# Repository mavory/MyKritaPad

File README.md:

# MyKritaPad

MyKritaPad is a custom 9-key macropad powered by a Seeed Studio XIAO RP2040!
It includes 9 mechanical switches wired through 9 diodes and two EC11 rotary encoders for additional input control. ⭐

## Why did I do this?

I wanted to try something completely new that I had never done before. I was very interested in how everyone can create their own mini keyboard, so I tried it too.

## Notes

I started on Friday, October 28th. That day I saw that I could make my own mini keyboard, I registered and downloaded the programs. Then I opened KiCad and told myself that I would never do it (it was like flying a plane for the first time). Well, I had to overcome myself and started creating with it. At first it was terrible, but somehow I got over it.

Unfortunately, on October 29th I got sick and couldn't do anything at all, but on November 30th I overcame myself and started creating the first designs for my KritaPad. When I created it with it, I moved to Fusion, which I also looked into, what it was... Somehow I did it, even though I don't want to think about it.

Then on December 1st I overcame myself and spent the whole day at the computer to finish it. In the evening I finished and submitted the project.

## Features
- 9 mechanical keys  
- 9x diodes for proper key isolation  
- 12x SK6812 MINI-E addressable RGB LEDs (RGB LEDs unfortunately I had a bad footprint and because of that my neopixels don't work)  
- 2x EC11 rotary encoders
- Powered by Seeed Studio XIAO RP2040  
- Designed for use with KMK or custom firmware  

## PCB
The PCB is designed in KiCad and includes:
- 9 key switch footprints  
- diode matrix wiring  
- daisy-chained SK6812 MINI-E LEDs 
- pins for two rotary encoders  
- XIAO RP2040 as the main controller  

### Schematic

### PCB Layout
(I know, it's terrible.)

### Top view

## Firmware
The macropad can be programmed using KMK,... or any custom RP2040 firmware.  

## BOM

### Custom Components
- 1x Custom PCB  
- 1x 3D printed case (top, bottom - Black)
- 9x keycaps  

### COTS Components
- 9x mechanical switches (MX style)  
- 9x Blank DSA keycaps
- 9x 1N4148 diodes  
- 12x SK6812 MINI-E LEDs  
- 2x EC11 rotary encoders  
- 1x Seeed Studio XIAO RP2040    
- 4x M3 x 6mm Screws
- 4x M3x5mx4mm heatset inserts

## Info
This macropad is made as part of the Hack Club Hackpad program! ✨

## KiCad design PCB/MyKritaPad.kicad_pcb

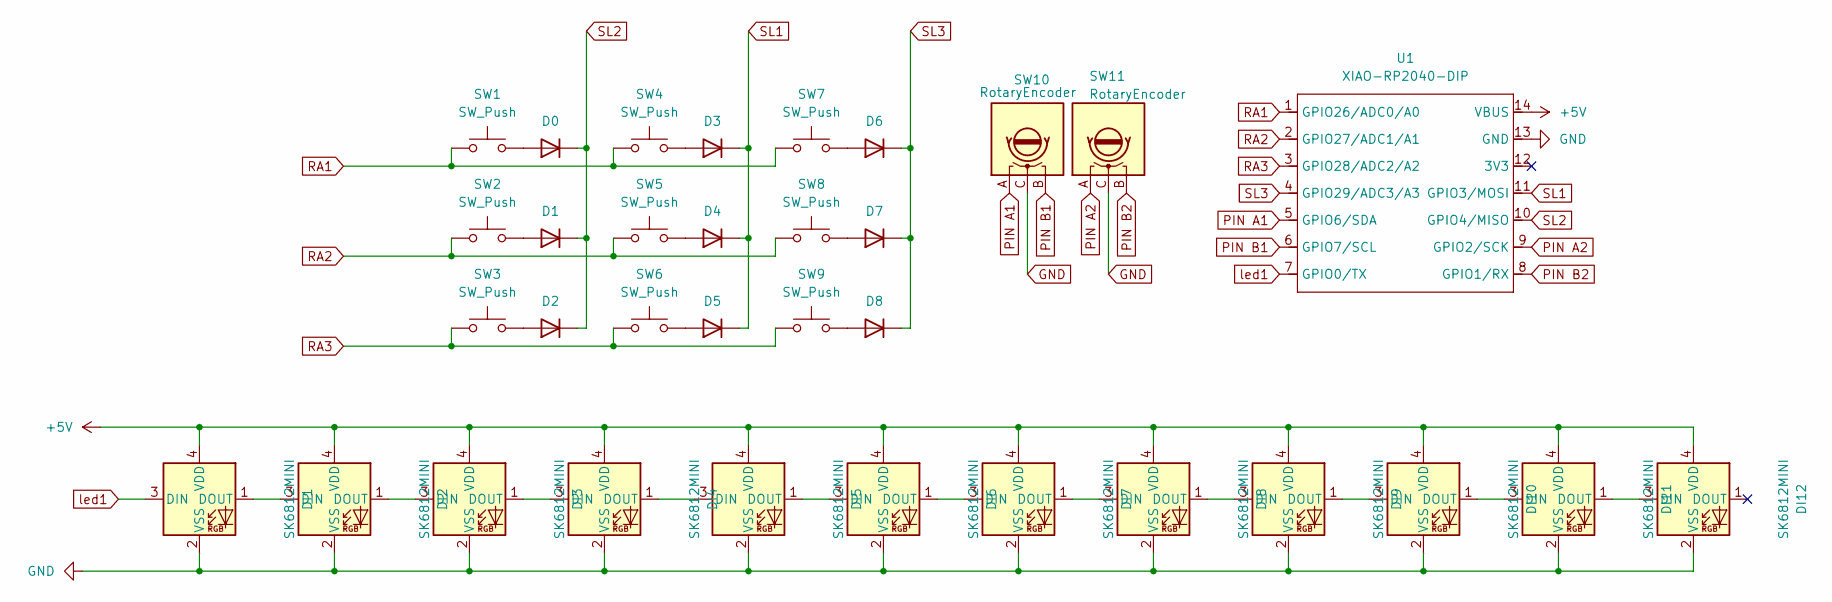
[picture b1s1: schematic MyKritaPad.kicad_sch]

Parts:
D0, D1, D2, D3, D4, D5, D6, D7, D8: 1N4148; D_DO-35_SOD27_P7.62mm_Horizontal
DI1, DI2, DI3, DI4, DI5, DI6, DI7, DI8, DI9, DI10, DI11, DI12: SK6812MINI; LED_SK6812MINI_PLCC4_3.5x3.5mm_P1.75mm
SW1, SW2, SW3, SW4, SW5, SW6, SW7, SW8, SW9: SW_Push; SW_Cherry_MX_1.00u_PCB
SW10, SW11: RotaryEncoder; RotaryEncoder_Alps_EC11E_Vertical_H20mm
U1: XIAO-RP2040-DIP

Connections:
+5V: DI1.4 (VDD), DI2.4 (VDD), DI3.4 (VDD), DI4.4 (VDD), DI5.4 (VDD), DI6.4 (VDD), DI7.4 (VDD), DI8.4 (VDD), DI9.4 (VDD), DI10.4 (VDD), DI11.4 (VDD), DI12.4 (VDD), U1.14 (VBUS)
GND: DI1.2 (VSS), DI2.2 (VSS), DI3.2 (VSS), DI4.2 (VSS), DI5.2 (VSS), DI6.2 (VSS), DI7.2 (VSS), DI8.2 (VSS), DI9.2 (VSS), DI10.2 (VSS), DI11.2 (VSS), DI12.2 (VSS), SW10.C, SW11.C, U1.13 (GND)
unnamed: D0.2 (A), SW1.2
unnamed: D1.2 (A), SW2.2
unnamed: D2.2 (A), SW3.2
unnamed: D3.2 (A), SW4.2
unnamed: D4.2 (A), SW5.2
unnamed: D5.2 (A), SW6.2
unnamed: D6.2 (A), SW7.2
unnamed: D7.2 (A), SW8.2
unnamed: D8.2 (A), SW9.2
unnamed: DI1.1 (DOUT), DI2.3 (DIN)
unnamed: DI2.1 (DOUT), DI3.3 (DIN)
unnamed: DI3.1 (DOUT), DI4.3 (DIN)
unnamed: DI4.1 (DOUT), DI5.3 (DIN)
unnamed: DI5.1 (DOUT), DI6.3 (DIN)
unnamed: DI6.1 (DOUT), DI7.3 (DIN)
unnamed: DI7.1 (DOUT), DI8.3 (DIN)
unnamed: DI8.1 (DOUT), DI9.3 (DIN)
unnamed: DI9.1 (DOUT), DI10.3 (DIN)
unnamed: DI10.1 (DOUT), DI11.3 (DIN)
unnamed: DI11.1 (DOUT), DI12.3 (DIN)
PIN A1: SW10.A, U1.5 (GPIO6/SDA)
PIN A2: SW11.A, U1.9 (GPIO2/SCK)
PIN B1: SW10.B, U1.6 (GPIO7/SCL)
PIN B2: SW11.B, U1.8 (GPIO1/RX)
RA1: SW1.1, SW4.1, SW7.1, U1.1 (GPIO26/ADC0/A0)
RA2: SW2.1, SW5.1, SW8.1, U1.2 (GPIO27/ADC1/A1)
RA3: SW3.1, SW6.1, SW9.1, U1.3 (GPIO28/ADC2/A2)
SL1: D3.1 (K), D4.1 (K), D5.1 (K), U1.11 (GPIO3/MOSI)
SL2: D0.1 (K), D1.1 (K), D2.1 (K), U1.10 (GPIO4/MISO)
SL3: D6.1 (K), D7.1 (K), D8.1 (K), U1.4 (GPIO29/ADC3/A3)
led1: DI1.3 (DIN), U1.7 (GPIO0/TX)

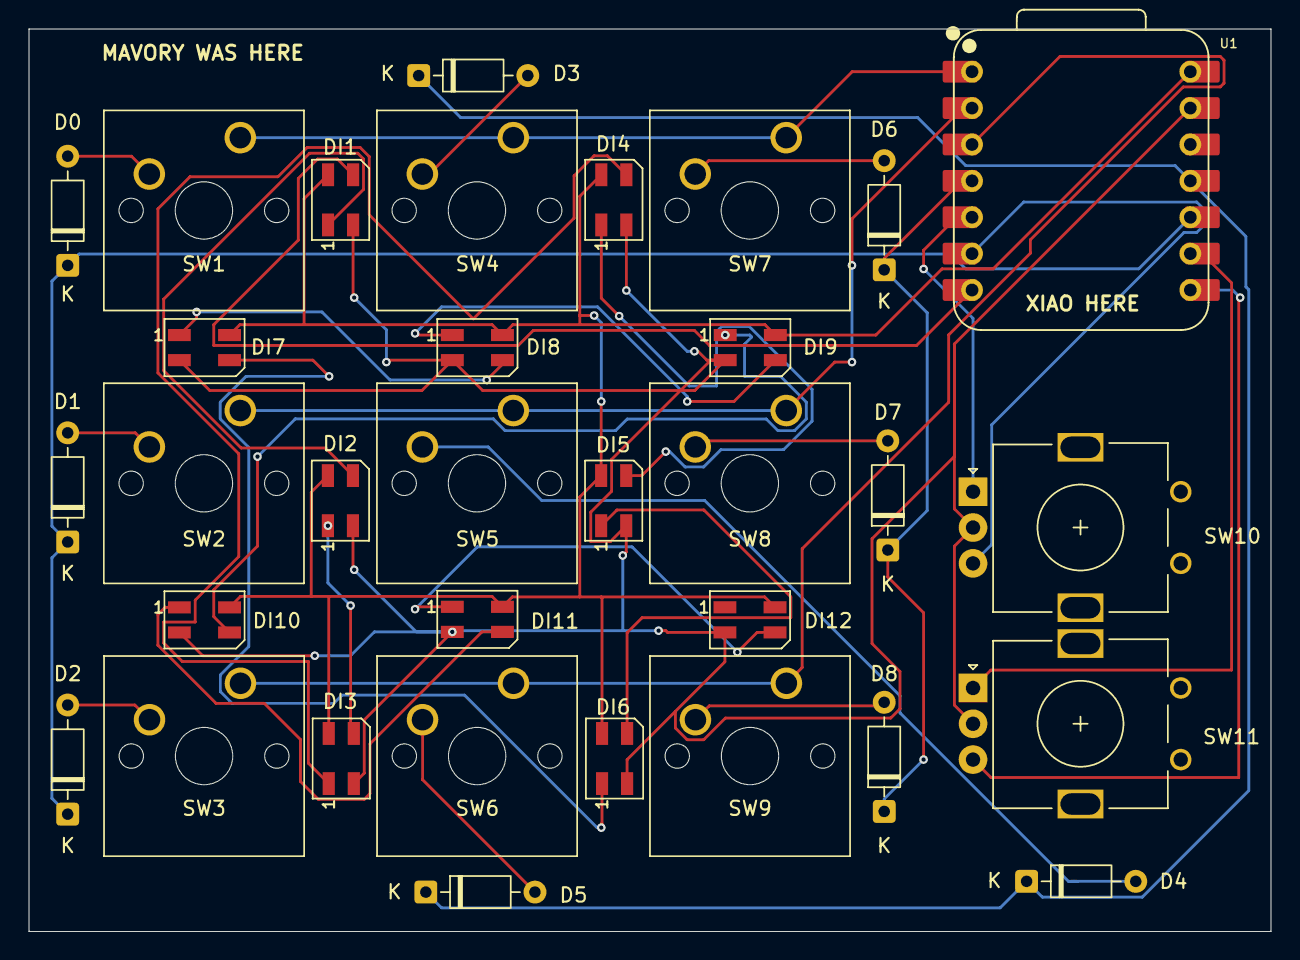
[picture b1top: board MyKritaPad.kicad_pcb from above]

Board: 2 copper layers, 86.7 x 63.0 mm, 33 parts (0 on the bottom side), 33 nets.

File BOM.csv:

"Reference","Qty","Value"
"D0,D1,D2,D3,D4,D5,D6,D7,D8","9","1N4148"
"DI1,DI2,DI3,DI4,DI5,DI6,DI7,DI8,DI9,DI10,DI11,DI12","12","SK6812MINI"
"SW1,SW2,SW3,SW4,SW5,SW6,SW7,SW8,SW9","9","SW_Push"
"SW10,SW11","2","RotaryEncoder"
"U1","1","XIAO-RP2040-DIP"

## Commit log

2025-12-01 Create CAD
2025-12-01 Create PCB
2025-12-01 Create Firmware
2025-12-01 Create idk
2025-12-01 Add PCB
2025-12-01 Image
2025-12-01 Update README with PCB layout note
    Added a note about the PCB layout quality.
2025-12-01 Schema
2025-12-01 Add schematic image to README
2025-12-01 Add PCB layout image to README
2025-12-01 Case
2025-12-01 Add star emoji to product description
2025-12-01 Update README to simplify rotary encoders description
2025-12-01 Add 'Top view' section to README
    Added a new section for 'Top view' with an image.
2025-12-01 Add firmware for 3x3 macropad with RGB effects
    Initial implementation of a 3x3 macropad with encoders and RGB LED effects.
2025-12-01 Add boot.py for KMK/CircuitPython configuration
2025-12-01 Create info
2025-12-01 Add new screenshot to README
    Added a new image to the README for additional context.
2025-12-01 Update case color in README
2025-12-01 3d_MODEL
2025-12-01 Update image in README for top view section
2025-12-01 Include personal project experience in README
    Added personal notes about the project experience.
2025-12-01 Add text to README
    Added a section explaining the motivation behind the project.
2025-12-01 Gerbers
2025-12-01 Add project notes and timeline to README
    Added personal notes about the project timeline and challenges faced during development.
2025-12-01 Add new image to README
    Added an additional image to the README for reference.
2025-12-01 Document journal entry on mini keyboard project
    Added a detailed journal entry documenting the process of creating a mini keyboard, including challenges faced and time spent.
2025-12-01 Don´t look 🧑‍🦽
2025-12-01 Fusion
2025-12-02 I edited the text at the bottom.
2025-12-02 New 3D model
2025-12-04 Photos
2025-12-04 Images
2025-12-04 3D models
2026-01-31 Filmware
    Refactor main.py to update encoder handling and RGB setup.
2026-01-31 Scripts
2026-01-31 Scripts
    Refactor keyboard setup and add layer reset functionality.
2026-01-31 Journal.md
    Updated journal entries with detailed progress on PCB project, including timelines, tasks completed, and time spent on each phase. Added images to illustrate the process.
2026-01-31 README.md
    Added an image to enhance the README with a visual representation of MyKritaPad.
2026-01-31 README.md
2026-01-31 README.md
    Removed mention of RGB LEDs not working due to footprint issue.
